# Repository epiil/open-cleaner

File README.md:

# opencleaner: open-source videotape cleaning

## Introduction

This repo contains instructions for assembling, testing, and operating an open-reel 1/2" magnetic videotape cleaner. When used in conjunction with other remediation treatments like incubation, tape cleaning assists in minimizing the effects of tape degradation such as binder hydrolysis ("sticky shed syndrome") during the playback/reformatting process.  

Controlled by an Arduino Uno microcontroller and integrated motor shield, the machine consists of a dual-motor spindle system that moves tape through two Pellon cleaning stations. Tape speed and tension are monitored through feedback from optical encoders attached to each motor's shaft. Each Pellon cleaning station incrementally advances fabric past several contact points.  

In-progress videos:

[02/15/2017 - 24VDC Motor Test](https://vimeo.com/204296759)

[02/23/2017 - PID Control Test](https://vimeo.com/205490774)

##Repository Contents:

- /hardware - contains .dwg, .pdf, .stp and .stl files for enclosure and spindle fabrication.

- /software - contains .ino Arduino sketches (http://www.arduino.cc/).

- /schematics - contains .sch and .pdf schematic files for individual components.

- /photos - photo gallery

## Acknowledgements

This project could not have been possible without the generous contributions from the following people and organizations:

Tim Woolaver

Mike Maxwell

Maurice Schechter

Video Data Bank - Tom Colley, Kristin McDonough

Smithsonian NMAAHC - Walter Forsberg

Signal Culture - Deborah Bernagozzi, Jason Bernagozzi, Hank Rudolph

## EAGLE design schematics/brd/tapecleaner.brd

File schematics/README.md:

- /ComponentSchematics - contains fact sheets for inividual components

- /png - contains .png image of associated schematic

- /sch - contains .sch schematic files done in Eagle (http://www.cadsoftusa.com/)

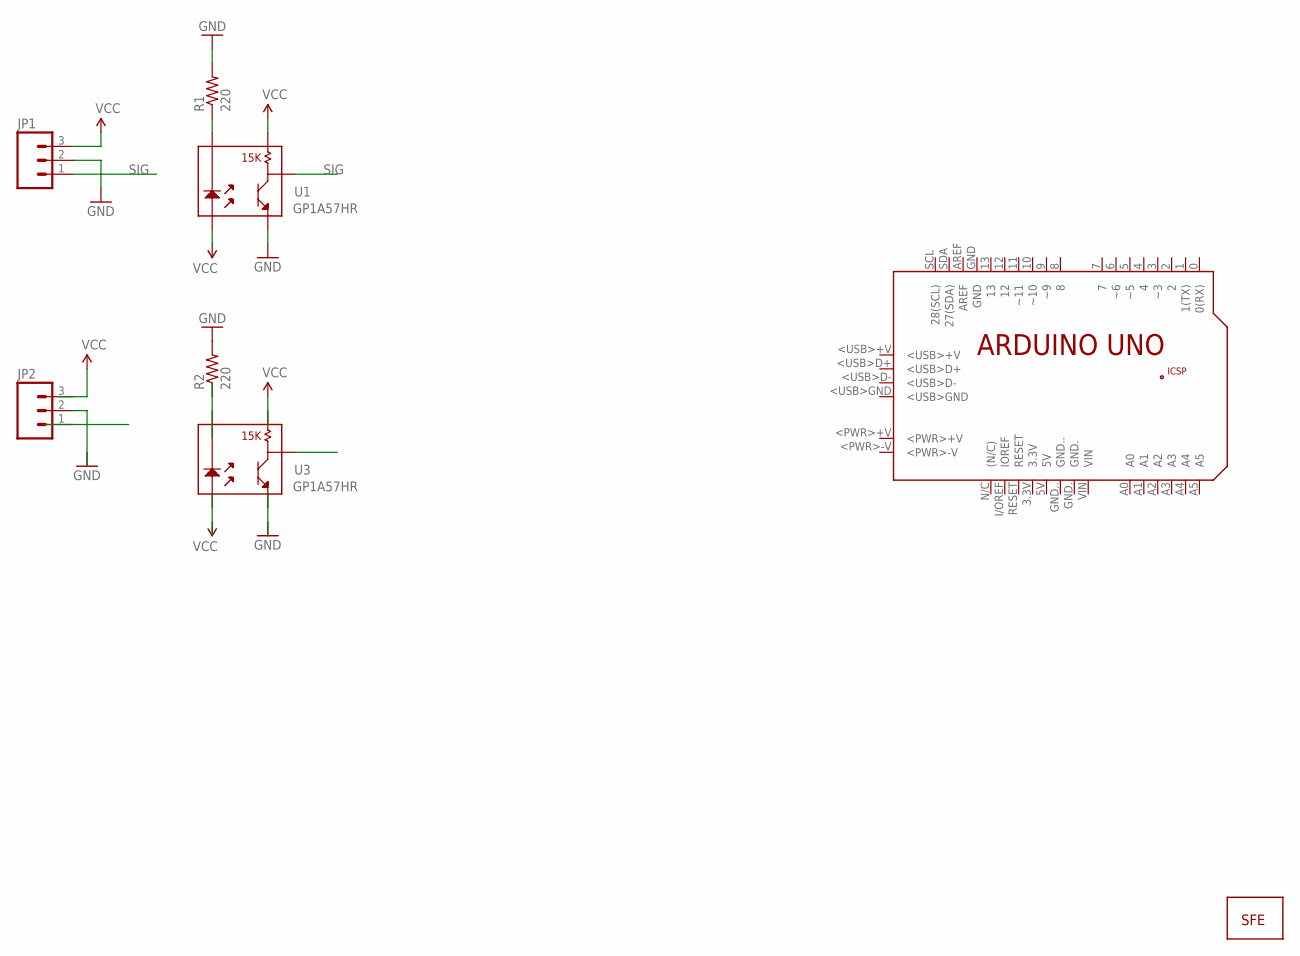
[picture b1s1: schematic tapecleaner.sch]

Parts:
JP1, JP2: M03PTH; 1X03
PCB1: ARDUINO_UNO
R1, R2: 220; AXIAL-0.3
U1, U3: GP1A57HR
U2: LOGO-SFESK; SFE-LOGO-FLAME

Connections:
GND: JP1.2, R1.P$2 (2), R2.P$2 (2), U1.5
unnamed: R1.P$1 (1), U1.2
SIG: JP1.1, U1.4
VCC: JP1.3, U1.1, U1.3

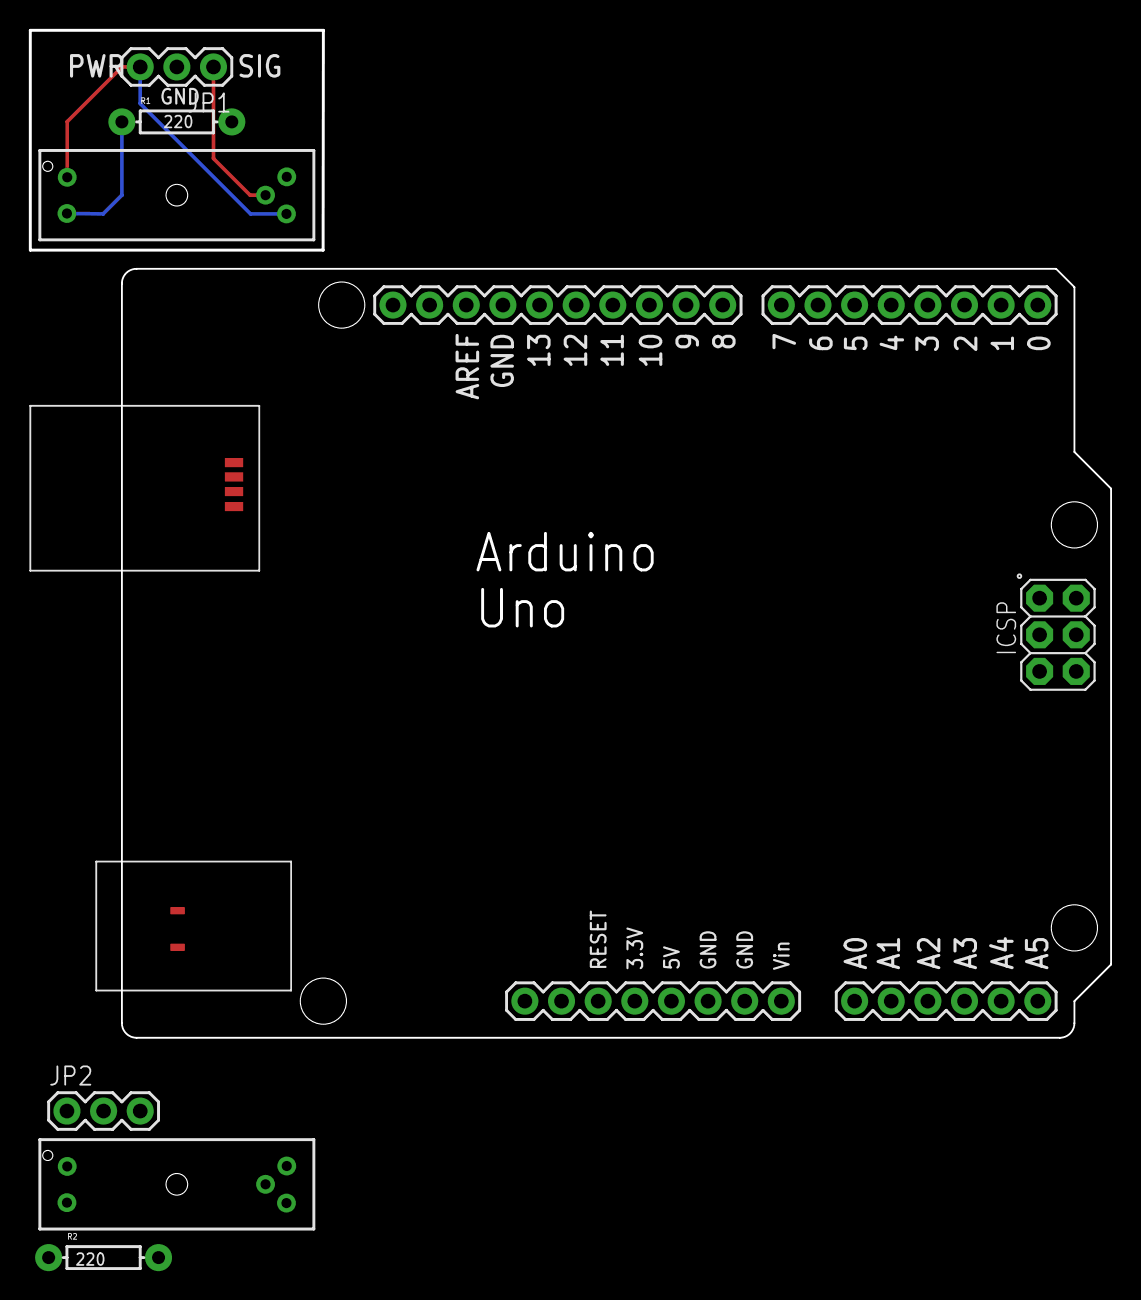
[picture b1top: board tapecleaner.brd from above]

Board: 2 copper layers, 74.9 x 69.8 mm, 8 parts (1 on the bottom side), 4 nets.

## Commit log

2014-10-14 first commit
    go
2014-10-14 removed old sketches
2014-10-14 motor and servo proper names
2014-10-14 Rename sketch_oct26a.ino to sketch_oct14.ino
2014-10-14 Added partslist
2014-10-14 added pictures
    spindle mod
2014-10-15 parameters
2014-10-22 Added OpenSCAD spindle layouts
    UMatic and 1/4” and 1/2” formats
2014-10-22 Added spindle STLs (work in progress)
2014-10-22 Update tree
2014-10-22 Added history.txt
2014-10-22 added arduino link
2014-10-22 update description
2014-10-22 added Adafruit motor shield schematic
2014-10-22 added servos, motors, pellon
2014-10-22 added pellon guide photos
2014-10-23 added SketchUp working files
2014-10-23 added pellon details
2014-10-23 added detail to sketch
2014-10-25 added UMatic spindle dimensions
2014-10-29 updated history.txt
2014-10-29 revised history.txt
2014-10-29 added DC potentiometer sketch
2014-10-29 added pellon gear motors
2014-10-31 added half-inch reel dimensions
2014-10-31 added 1/4" spindle dimensions
2014-10-31 cleaned up misc
2014-10-31 individual format folders
2014-10-31 ino folder
2014-10-31 Added spindle dimensions
2014-11-04 added addl umat spindle dimensions
2014-11-04 updated umatic spindle
2014-11-04 added half-inch spindle
2014-11-05 cleaner sketch in tinkercad
2014-11-07 added Fritzing schematics
2014-11-10 removed Adafruit schematic
2014-11-10 added legacy folder
2014-11-10 Cleaned up file naming, added legacy folder
2014-11-10 updated parts and price list
2014-11-13 added motor shield schematics
2014-11-14 added initial DC motor sketch
2014-11-14 cleaned up legacy sketches
2014-11-15 added Arduino motor direction sketches
2014-11-15 updated circuit diagrams
2014-11-16 Added parts - optos and breakout
2014-11-16 added DPDT and SPDT switches
2014-11-16 cleaned up file naming
2014-11-17 updated parts list
2014-11-20 added photo interrupter sketch test
2015-01-16 added take-up spindles
2015-01-27 added 3D printed umat spindle prototype
2015-02-09 spindles
2015-02-10 umat spindle details
2015-02-11 umat
2015-02-23 changed to markdown
2015-03-10 add GNU public license
2015-03-10 additional infrared sensors
2015-03-10 added aluminum enclosure
2015-03-10 start enclosure top cutouts
2015-03-11 top enclosure
2015-03-11 enclosure top update
2015-03-11 2D scad and dxf
2015-03-11 2D and 3D enclosure top
2015-03-11 update hist
2015-03-11 removed legacy
2015-03-11 scads and stls with combined parts
2015-03-11 updated sketch
2015-03-11 scad updates
2015-03-12 updated scad and stl
2015-03-12 update scad, stl
2015-03-12 updated enclosure scad, stl, 2d and 3d
2015-03-13 updated scad
2015-03-13 update scad
2015-03-13 updated stl
2015-03-13 update parts scad
2015-03-13 adjusted pellon rolls
2015-03-13 update scads and dxf
2015-03-13 added photoops and IR sensors
2015-03-13 individual scads for objects
2015-03-13 added side scads
2015-03-14 updated STL and SCAD
2015-03-15 updated STL and SCAD - revised roller guides
2015-03-15 STL and SCAD - motor spindle
2015-03-15 2D finalized DXF for front and back panels
2015-03-16 deleted old STL, cleaned up filenaming convention
2015-03-16 updated SCAD, STL, DXF - adjustable guide slots
2015-03-16 updated UMatic spindle STL and SCAD
2015-03-16 added wiggle-room in roller cutouts
2015-03-17 removed introduction, edited license
2015-03-18 updated history, cleaned up files, etc.
2015-03-19 adjusted top width to 15.36"
2015-03-19 intro draft and cleaning
2015-03-19 cleaned up file naming and directory
2015-03-20 intro language
2015-03-20 readme edit
2015-03-21 revised Umatic spindle prongs
2015-03-22 updated Umatic spindle high render quality
2015-03-23 updated partslist
2015-03-24 preliminary Arduino sketch
2015-03-26 draft schematic
2015-03-28 updated schem
2015-03-29 updated scheme
2015-04-01 um um
2015-04-02 in-progress sketches
2015-04-02 added both motors
2015-04-03 updated main sketch - lcd, ir, photo interrupters
2015-04-04 updated fritz scheme, added pollen motors test sketch
2015-04-04 Moved schematics from Fritzing to Eagle
2015-04-05 removed .brd file, updated schematic
2015-04-05 arduino sketch header
2015-04-05 updated main 3d scad sketch
2015-04-06 main sketch testing
2015-04-07 updated sketch with IR read/write
2015-05-12 formatting / fix grammar
2015-05-23 added in-progress photos folder
2015-05-23 photo formatting
2015-05-23 begin design narrative
2015-05-23 start design narrative
2015-05-23 updated parts list and tapecleaner SCAD
2015-05-23 fixed interrupter typo
2015-05-23 photo cropping
2015-05-23 photo format 2
2015-05-23 add tape cleaner layout diagrams
2015-05-27 added IR distance sensor holder
2015-05-27 ir distance sensor holder formatting
2015-05-27 refined IR distance sensor holder
2015-05-27 start roller scads
2015-05-28 work on 1/2" roller
2015-05-31 added M3 screws and hex nuts
2015-06-01 refined Umatic spindle
2015-06-01 added photointerrupter holders
2015-06-02 corrected measurements for rollers
2015-06-02 2nd design for roller
2015-06-03 revised LCD hex screws from M3 to M2
2015-06-05 revised PI holder
2015-06-13 parts list dump
2015-06-13 fixed fomatting
2015-06-13 added switch
2015-06-14 added usb cables and connector
2015-06-14 added parts price list CSV
2015-06-15 added LCD keypad holes - front panel
2015-06-18 removed depreciated sketch/libraries
2015-06-18 added Adafruit libraries
2015-07-05 roller guide update
2015-07-06 updated roller with corrected diameter
2015-07-06 updated parts list with roller spindle kits
2015-07-06 added bias to rollers
2015-07-06 removed depreciated roller sketch
2015-07-06 another roller update
2015-07-24 added 0.9.0 sketch
    removed depreciated sketches, started version control
2015-07-25 added wiring photos
2015-07-25 0.9.0.1
2015-07-25 removed dead links
2015-07-25 removed dead link
2015-08-01 added linear pot spec sheet
2015-08-02 Major partslist update
2015-08-02 updated partslist and pricelist
2015-08-02 added hookup wire and 1K resistor
2015-08-02 updated with formatting
2015-08-02 removed IR sensor mounts, interrupter mounts
2015-08-02 updated photo descriptions
2015-08-02 format to markdown
2015-08-02 removed history to update
2015-08-02 removed narrative for update
2015-08-02 updated schematic with README
2015-08-02 0.9.0.2
2015-08-02 formatting
2015-08-02 renamed rollers
2015-08-02 copy editing
2015-08-03 0.9.0.3
2015-08-04 updated photos
2015-08-05 embed link
2015-08-05 photos folder
2015-08-05 embedded images in markdown
2015-08-07 begin main enclosure scad revision
2015-08-17 more photos
2015-08-17 photo links
2015-08-17 0.9.0.4
2015-08-20 added pellon mount STL
2015-08-20 pellon mounts scad and stl
2015-08-27 add mounting hub schematics
2015-09-29 updated precision roller
    +fabrication drawing
    +stl
    +dwg
    +stp
    -scad
2015-12-16 0.9.0.5 sketch + photos
2015-12-16 initial assembly instructions commit
2015-12-16 updated assembly photos
2015-12-19 updated assembly instructions.
2015-12-19 fix typo
2015-12-19 updated main README
2016-02-13 new software and schematics
2016-02-13 photo dump proto 2
2016-02-13 new enclosure photos
2016-02-14 proto II bom
2016-02-15 cleaned up structure
2016-02-15 updated spindle schematics
2016-02-15 VDB 30 min sketch
2016-02-28 hardware schematics, EEPROM & PID libraries
2016-04-12 SC dump
2016-04-12 typo
2016-04-12 wrong photo
2017-01-17 remove depreciated documentation, update to come
2017-02-25 updated repo, new PID code, etc.
2017-02-25 fix image link
2017-02-26 rm .DS_Store
2017-02-26 updated BoM
2017-03-25 updated Illustrator enclosure files with cutouts
2017-03-26 enlarged cutout for LCD keypad
2017-03-26 ACE mounts for 3D printing (in-progress)
2017-08-05 house cleaning
2017-08-05 house cleaning 2
